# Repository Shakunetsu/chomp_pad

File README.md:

# chomp_pad
Work in progress split keyboard edited to my tastes.

Don't know when I'll ever finish it, but I hope I will one day because I'm still not happy with any currently available option.

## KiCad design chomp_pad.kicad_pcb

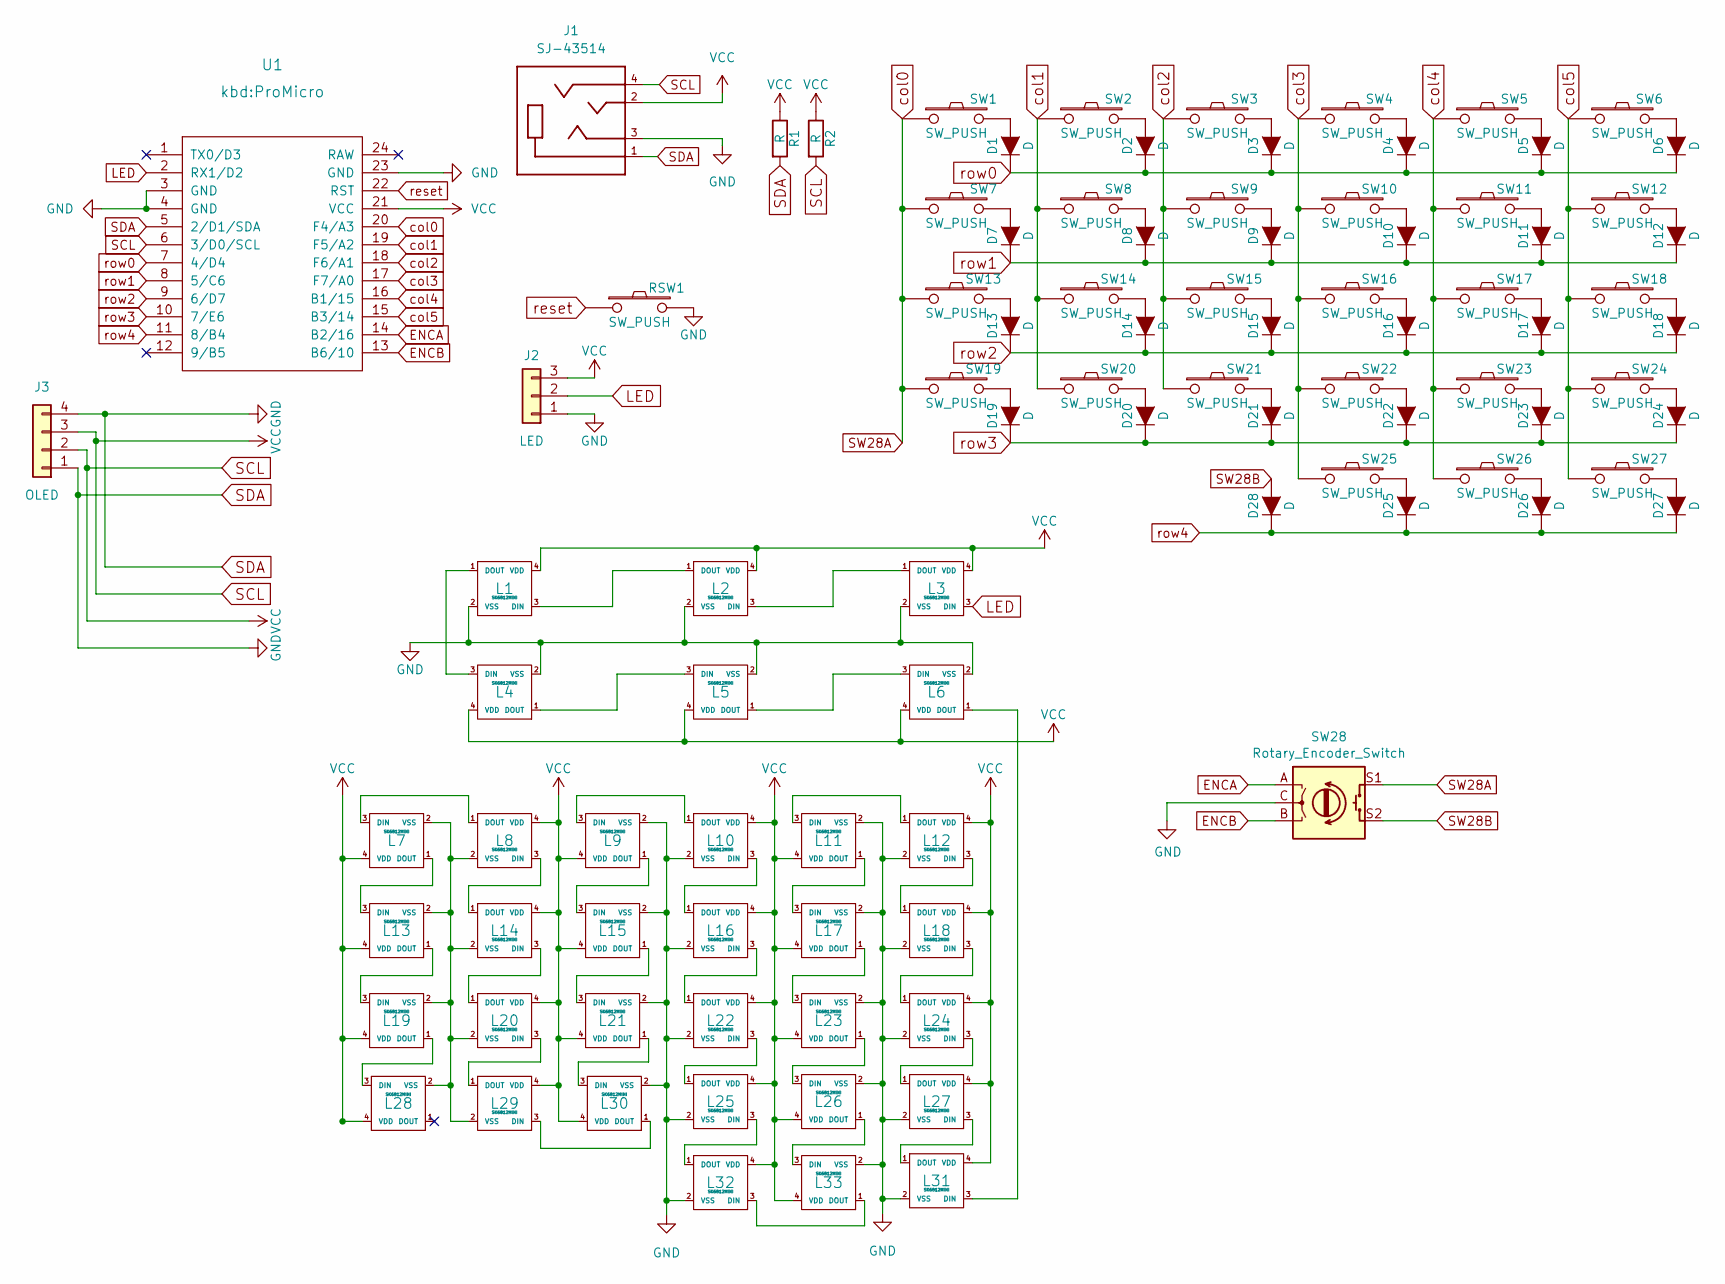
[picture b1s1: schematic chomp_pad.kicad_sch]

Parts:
D1, D2, D3, D4, D5, D6, D7, D8, D9, D10, D11, D12, D13, D14, D15, D16, D17, D18, D19, D20, D21, D22, D23, D24, D25, D26, D27, D28: D
J1: SJ-43514; PART_REV 1.04
J2: LED
J3: OLED
L1, L2, L3, L4, L5, L6, L7, L8, L9, L10, L11, L12, L13, L14, L15, L16, L17, L18, L19, L20, L21, L22, L23, L24, L25, L26, L27, L28, L29, L30, L31, L32, L33: SK6812MINI
R1, R2: R
RSW1: SW_PUSH
SW1, SW2, SW3, SW4, SW5, SW6, SW7, SW8, SW9, SW10, SW11, SW12, SW13, SW14, SW15, SW16, SW17, SW18, SW19, SW20, SW21, SW22, SW23, SW24, SW25, SW26, SW27: SW_PUSH
SW28: Rotary_Encoder_Switch
U1: kbd:ProMicro

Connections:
ENCA: SW28.A, U1.14 (B2/16)
ENCB: SW28.B, U1.13 (B6/10)
LED: J2.2, L3.3 (DIN), U1.2 (RX1/D2)
unnamed: D1.2 (A), SW1.2
unnamed: D2.2 (A), SW2.2
unnamed: D3.2 (A), SW3.2
unnamed: D4.2 (A), SW4.2
unnamed: D5.2 (A), SW5.2
unnamed: D6.2 (A), SW6.2
unnamed: D7.2 (A), SW7.2
unnamed: D8.2 (A), SW8.2
unnamed: D9.2 (A), SW9.2
unnamed: D10.2 (A), SW10.2
unnamed: D11.2 (A), SW11.2
unnamed: D12.2 (A), SW12.2
unnamed: D13.2 (A), SW13.2
unnamed: D14.2 (A), SW14.2
unnamed: D15.2 (A), SW15.2
unnamed: D16.2 (A), SW16.2
unnamed: D17.2 (A), SW17.2
unnamed: D18.2 (A), SW18.2
unnamed: D19.2 (A), SW19.2
unnamed: D20.2 (A), SW20.2
unnamed: D21.2 (A), SW21.2
unnamed: D22.2 (A), SW22.2
unnamed: D23.2 (A), SW23.2
unnamed: D24.2 (A), SW24.2
unnamed: D25.2 (A), SW25.2
unnamed: D26.2 (A), SW26.2
unnamed: D27.2 (A), SW27.2
unnamed: L1.1 (DOUT), L4.3 (DIN)
unnamed: L1.3 (DIN), L2.1 (DOUT)
unnamed: L2.3 (DIN), L3.1 (DOUT)
unnamed: L4.1 (DOUT), L5.3 (DIN)
unnamed: L5.1 (DOUT), L6.3 (DIN)
unnamed: L7.3 (DIN), L8.1 (DOUT)
unnamed: L9.3 (DIN), L10.1 (DOUT)
unnamed: L10.3 (DIN), L16.1 (DOUT)
unnamed: L11.1 (DOUT), L17.3 (DIN)
unnamed: L11.3 (DIN), L12.1 (DOUT)
unnamed: L12.3 (DIN), L18.1 (DOUT)
unnamed: L13.1 (DOUT), L19.3 (DIN)
unnamed: L7.2 (VSS), L8.2 (VSS), L13.2 (VSS), L14.2 (VSS), L19.2 (VSS), L20.2 (VSS), L28.2 (VSS), L29.2 (VSS)
unnamed: L7.1 (DOUT), L13.3 (DIN)
unnamed: L8.3 (DIN), L14.1 (DOUT)
unnamed: L14.3 (DIN), L20.1 (DOUT)
unnamed: L15.1 (DOUT), L21.3 (DIN)
unnamed: L9.1 (DOUT), L15.3 (DIN)
unnamed: L16.3 (DIN), L22.1 (DOUT)
unnamed: L17.1 (DOUT), L23.3 (DIN)
unnamed: L18.3 (DIN), L24.1 (DOUT)
unnamed: L19.1 (DOUT), L28.3 (DIN)
unnamed: L20.3 (DIN), L29.1 (DOUT)
unnamed: L21.1 (DOUT), L30.3 (DIN)
unnamed: L22.3 (DIN), L25.1 (DOUT)
unnamed: L23.1 (DOUT), L26.3 (DIN)
unnamed: L24.3 (DIN), L27.1 (DOUT)
unnamed: L25.3 (DIN), L32.1 (DOUT)
unnamed: L26.1 (DOUT), L33.3 (DIN)
unnamed: L27.3 (DIN), L31.1 (DOUT)
unnamed: L29.3 (DIN), L30.1 (DOUT)
unnamed: L6.1 (DOUT), L31.3 (DIN)
unnamed: L32.3 (DIN), L33.1 (DOUT)
SCL: J1.2, J1.4, J2.3, J3.2, J3.3, L1.4 (VDD), L2.4 (VDD), L3.4 (VDD), L4.4 (VDD), L5.4 (VDD), L6.4 (VDD), L7.4 (VDD), L8.4 (VDD), L9.4 (VDD), L10.4 (VDD), L11.4 (VDD), L12.4 (VDD), L13.4 (VDD), L14.4 (VDD), L15.4 (VDD), L16.4 (VDD), L17.4 (VDD), L18.4 (VDD), L19.4 (VDD), L20.4 (VDD), L21.4 (VDD), L22.4 (VDD), L23.4 (VDD), L24.4 (VDD), L25.4 (VDD), L26.4 (VDD), L27.4 (VDD), L28.4 (VDD), L29.4 (VDD), L30.4 (VDD), L31.4 (VDD), L32.4 (VDD), L33.4 (VDD), R1.1, R2.1, R2.2, U1.6 (3/D0/SCL), U1.21 (VCC)
SDA: J1.1, J1.3, J2.1, J3.1, J3.4, L1.2 (VSS), L2.2 (VSS), L3.2 (VSS), L4.2 (VSS), L5.2 (VSS), L6.2 (VSS), L9.2 (VSS), L10.2 (VSS), L11.2 (VSS), L12.2 (VSS), L15.2 (VSS), L16.2 (VSS), L17.2 (VSS), L18.2 (VSS), L21.2 (VSS), L22.2 (VSS), L23.2 (VSS), L24.2 (VSS), L25.2 (VSS), L26.2 (VSS), L27.2 (VSS), L30.2 (VSS), L31.2 (VSS), L32.2 (VSS), L33.2 (VSS), R1.2, RSW1.2, SW28.C, U1.3 (GND), U1.4 (GND), U1.5 (2/D1/SDA), U1.23 (GND)
SW28A: SW1.1, SW7.1, SW13.1, SW19.1, SW28.S1, U1.20 (F4/A3)
SW28B: D28.2 (A), SW28.S2
col1: SW2.1, SW8.1, SW14.1, SW20.1, U1.19 (F5/A2)
col2: SW3.1, SW9.1, SW15.1, SW21.1, U1.18 (F6/A1)
col3: SW4.1, SW10.1, SW16.1, SW22.1, SW25.1, U1.17 (F7/A0)
col4: SW5.1, SW11.1, SW17.1, SW23.1, SW26.1, U1.16 (B1/15)
col5: SW6.1, SW12.1, SW18.1, SW24.1, SW27.1, U1.15 (B3/14)
reset: RSW1.1, U1.22 (RST)
row0: D1.1 (K), D2.1 (K), D3.1 (K), D4.1 (K), D5.1 (K), D6.1 (K), U1.7 (4/D4)
row1: D7.1 (K), D8.1 (K), D9.1 (K), D10.1 (K), D11.1 (K), D12.1 (K), U1.8 (5/C6)
row2: D13.1 (K), D14.1 (K), D15.1 (K), D16.1 (K), D17.1 (K), D18.1 (K), U1.9 (6/D7)
row3: D19.1 (K), D20.1 (K), D21.1 (K), D22.1 (K), D23.1 (K), D24.1 (K), U1.10 (7/E6)
row4: D25.1 (K), D26.1 (K), D27.1 (K), D28.1 (K), U1.11 (8/B4)

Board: 2 copper layers, 96 parts (0 on the bottom side), 78 nets, no tracks yet.

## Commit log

2022-04-30 initialized
    go go go
2022-04-30 add submodules
2022-04-30 Add footprint libraries
2022-05-01 dunno
2022-05-09 fuck ocean
2022-05-10 done?
    i think this is done
2022-05-18 idk what i did
    final touches to schematic, loaded footprints.
2022-05-18 before pcb
2022-05-18 rename
    renamed to chomp_pad
2022-05-18 getting started
    starting PCB
2022-05-18 sleepy
    did a lot, need to fix dependencies on footprints but too lazy to
2022-05-18 fixed footprint and symbol dependencies
    still need to do 3d files but screw that
